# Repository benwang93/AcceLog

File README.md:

AcceLog - Accelerometer Log for Android
=======================================

Android
-------
This project uses the Adafruit MMA8451 breakout board connected to an Arduino Uno. The sensor and Arduino hardware can be easily modified. Eventually a custom board and enclosure should be built.

Links:
- Adafruit MMA8451 webpage:    adafru.it/2019
- Adafruit Arduino libraries:  https://learn.adafruit.com/adafruit-mma8451-accelerometer-breakout/wiring-and-test

The Arduino code and libraries are included in the Arduino folder in this repository.

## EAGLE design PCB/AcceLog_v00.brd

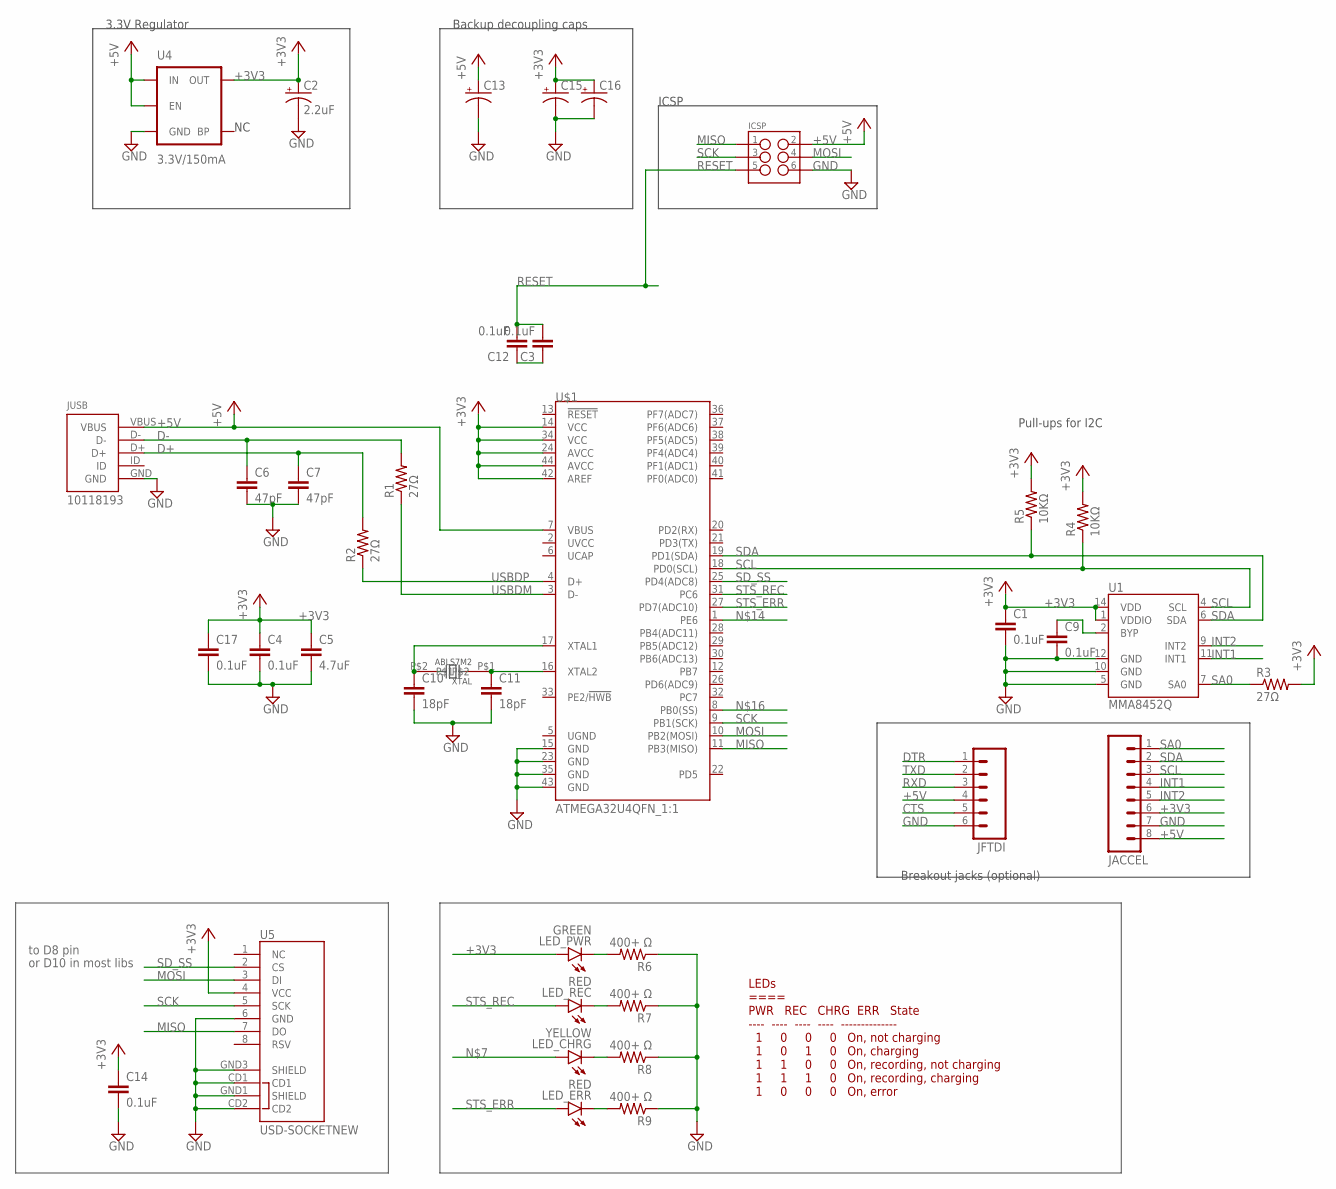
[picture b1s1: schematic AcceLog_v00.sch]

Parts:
C1, C3, C4, C9, C12, C14, C17: 0.1uF; 0603-CAP
C2: 2.2uF; EIA3216
C5: 4.7uF; 0603-CAP
C6, C7: 47pF; 0603-CAP
C10, C11: 18pF; 0603-CAP
C13, C15, C16: CPOL-USE2-5; E2-5
ICSP: M03X22X3_SILK_MALE_PTH; 2X3
JACCEL: M08LOCK; 1X08_LOCK
JFTDI: M06LOCK; 1X06_LOCK
JUSB: 10118193
LED_CHRG: YELLOW; LED-0603
LED_ERR: RED; LED-0603
LED_PWR: GREEN; LED-0603
LED_REC: RED; LED-0603
R1, R2, R3: 27Ω; 0603-RES
R4, R5: 10KΩ; 0603-RES
R6, R7, R8, R9: 400+ Ω; 0603-RES
U1: MMA8452Q; QFN-16_0.5MM
U4: 3.3V/150mA; SOT23-5
U5: USD-SOCKETNEW; MICRO-SD-SOCKET-PP
U$1: ATMEGA32U4QFN_1:1; QFN-44-NOPAD_1:1
XTAL: ABLS7M2

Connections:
+3V3: C1.1, C2.A (+), C4.1, C5.1, C14.1, C15.+, C16.+, C17.1, JACCEL.6, LED_PWR.A, R3.2, R4.2, R5.2, U1.1 (VDDIO), U1.14 (VDD), U4.5 (OUT), U5.4 (VCC), U$1.14 (VCC), U$1.24 (AVCC), U$1.34 (VCC), U$1.42 (AREF), U$1.44 (AVCC)
+5V: C13.+, ICSP.2, JACCEL.8, JFTDI.4, JUSB.VBUS, U4.1 (IN), U4.3 (EN), U$1.7 (VBUS)
CTS: JFTDI.5
D+: C7.1, JUSB.D+, R2.2
D-: C6.1, JUSB.D-, R1.2
DTR: C3.1, C12.1, JFTDI.1
GND: C1.2, C2.C (-), C4.2, C5.2, C6.2, C7.2, C9.2, C10.2, C11.2, C13.-, C14.2, C15.-, C16.-, C17.2, ICSP.6, JACCEL.7, JFTDI.6, JUSB.GND, R6.1, R7.1, R8.1, R9.1, U1.5 (GND), U1.10 (GND), U1.12 (GND), U4.2 (GND), U5.6 (GND), U5.CD1, U5.CD2, U5.GND1 (SHIELD), U5.GND3 (SHIELD), U$1.15 (GND), U$1.23 (GND), U$1.35 (GND), U$1.43 (GND)
INT1: JACCEL.4, U1.11 (INT1)
INT2: JACCEL.5, U1.9 (INT2)
MISO: ICSP.1, U5.7 (DO), U$1.11 (PB3(MISO))
MOSI: ICSP.4, U5.3 (DI), U$1.10 (PB2(MOSI))
unnamed: LED_PWR.C, R6.2
unnamed: LED_REC.C, R7.2
unnamed: LED_CHRG.C, R8.2
unnamed: LED_ERR.C, R9.2
unnamed: C10.1, U$1.17 (XTAL1), XTAL.P$2
unnamed: C9.1, U1.2 (BYP)
unnamed: C11.1, U$1.16 (XTAL2), XTAL.P$1
RESET: C3.2, C12.2, ICSP.5
RXD: JFTDI.3
SA0: JACCEL.1, R3.1, U1.7 (SA0)
SCK: ICSP.3, U5.5 (SCK), U$1.9 (PB1(SCK))
SCL: JACCEL.3, R4.1, U1.4 (SCL), U$1.18 (PD0(SCL))
SDA: JACCEL.2, R5.1, U1.6 (SDA), U$1.19 (PD1(SDA))
SD_SS: U5.2 (CS), U$1.25 (PD4(ADC8))
STS_ERR: LED_ERR.A, U$1.27 (PD7(ADC10))
STS_REC: LED_REC.A, U$1.31 (PC6)
TXD: JFTDI.2
USBDM: R1.1, U$1.3 (D-)
USBDP: R2.1, U$1.4 (D+)

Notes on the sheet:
3.3V Regulator
Pull-ups for I2C
ICSP
Backup decoupling caps
Breakout jacks (optional)
LEDs ==== PWR REC CHRG ERR State ---- ---- ---- ---- -------------- 1 0 0 0 On, not charging 1 0 1 0 On, charging 1 1 0 0 On, recording, not charging 1 1 1 0 On, recording, charging 1 0 0 0 On, error
to D8 pin
or D10 in most libs

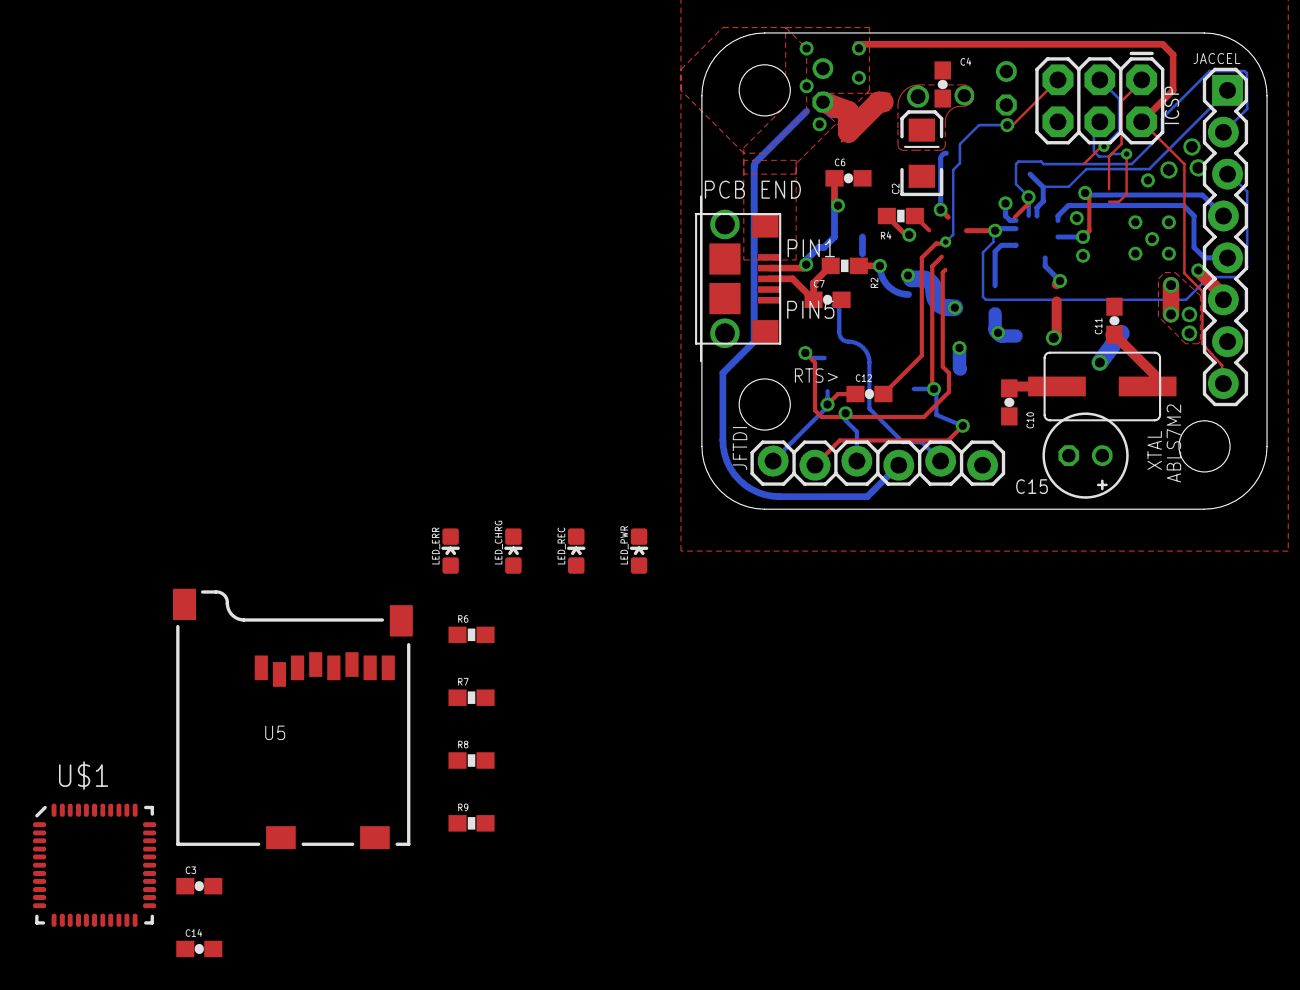
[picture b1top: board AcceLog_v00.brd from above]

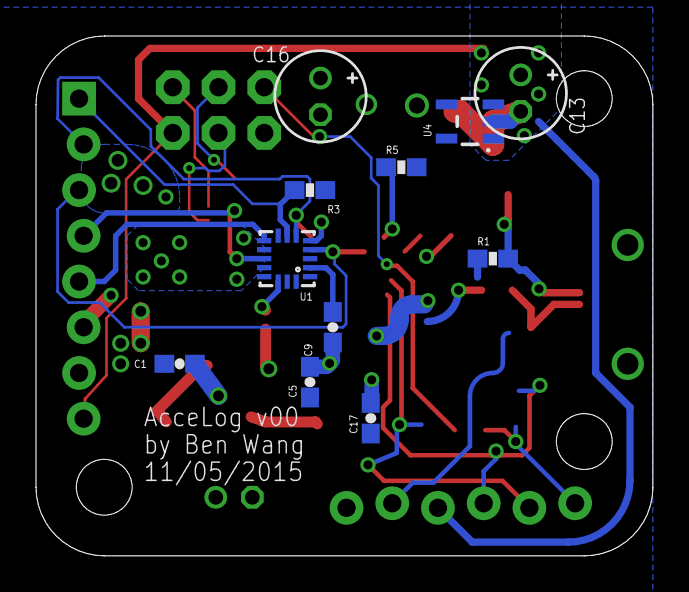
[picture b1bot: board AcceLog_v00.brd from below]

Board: 2 copper layers, 34.3 x 28.9 mm, 38 parts (11 on the bottom side), 27 nets.

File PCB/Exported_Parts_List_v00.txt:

Partlist

Exported from AcceLog_v01.sch at 11/5/2015 2:57 PM

EAGLE Version 7.3.0 Copyright (c) 1988-2015 CadSoft

Assembly variant: 

Part     Value           Device                 Package      Library             Sheet

C1       0.1uF           CAP0603-CAP            0603-CAP     SparkFun-Passives   1
C2       2.2uF           CAP_POL1206            EIA3216      SparkFun-Capacitors 1
C3       0.1uF           CAP0603-CAP            0603-CAP     SparkFun-Passives   1
C4       0.1uF           CAP0603-CAP            0603-CAP     SparkFun-Passives   1
C5       4.7uF           CAP0603-CAP            0603-CAP     SparkFun-Passives   1
C6       47pF            CAP0603-CAP            0603-CAP     SparkFun-Passives   1
C7       47pF            CAP0603-CAP            0603-CAP     SparkFun-Passives   1
C8       100nF           CAP0603-CAP            0603-CAP     SparkFun-Passives   1
C9       0.1uF           CAP0603-CAP            0603-CAP     SparkFun-Passives   1
C10      18pF            CAP0603-CAP            0603-CAP     SparkFun-Passives   1
C11      18pF            CAP0603-CAP            0603-CAP     SparkFun-Passives   1
C12      0.1uF           CAP0603-CAP            0603-CAP     SparkFun-Passives   1
C13                      CPOL-USE2-5            E2-5         rcl                 1
C15                      CPOL-USE2-5            E2-5         rcl                 1
C16                      CPOL-USE2-5            E2-5         rcl                 1
C17      0.1uF           CAP0603-CAP            0603-CAP     SparkFun-Passives   1
ICSP                     M03X22X3_SILK_MALE_PTH 2X3          SparkFun-Connectors 1
JACCEL                   M08LOCK                1X08_LOCK    SparkFun-Connectors 1
JFTDI                    M06LOCK                1X06_LOCK    SparkFun-Connectors 1
JUSB     10118193        10118193               10118193     MicroUSB            1
R1       27?             RESISTOR0603-RES       0603-RES     SparkFun-Passives   1
R2       27?             RESISTOR0603-RES       0603-RES     SparkFun-Passives   1
R3       27?             RESISTOR0603-RES       0603-RES     SparkFun-Passives   1
R4       10K?            RESISTOR0603-RES       0603-RES     SparkFun-Passives   1
R5       10K?            RESISTOR0603-RES       0603-RES     SparkFun-Passives   1
U1       MMA8452Q        MMA8452Q               QFN-16_0.5MM SparkFun-Sensors    1
U2       FTS31XS-U       FT231XS                SSOP20_L     SparkFun-DigitalIC  1
U3       ATMEGA328P_TQFP ATMEGA328P_TQFP        TQFP32-08    SparkFun-DigitalIC  1
U4       3.3V/150mA      V_REG_MIC52053.3V      SOT23-5      SparkFun-PowerIC    1
XTAL     ABLS7M2         ABLS7M2                ABLS7M2      AcceLogLib          1

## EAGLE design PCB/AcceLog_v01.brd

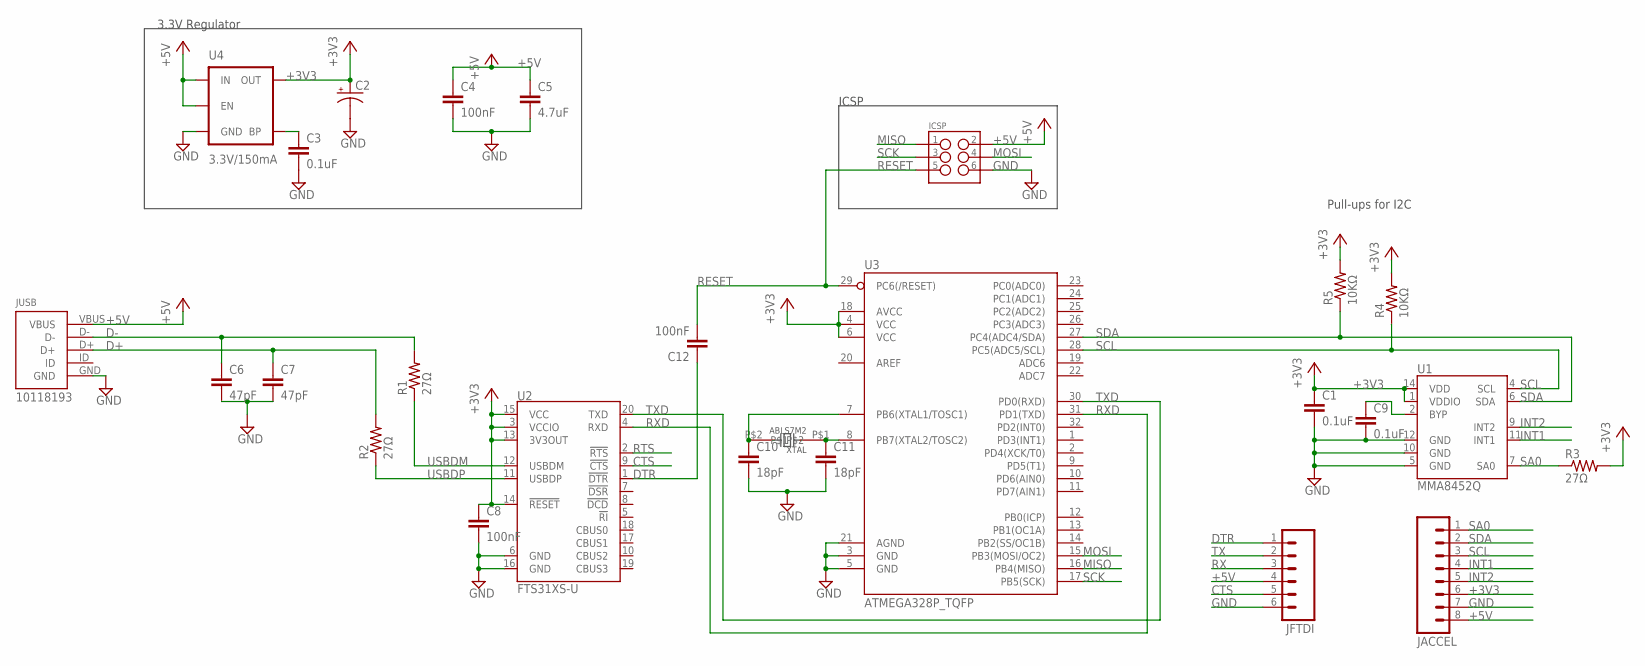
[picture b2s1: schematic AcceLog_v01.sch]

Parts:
C1, C3, C9: 0.1uF; 0603-CAP
C2: CAP_POL1206; EIA3216
C4, C8, C12: 100nF; 0603-CAP
C5: 4.7uF; 0603-CAP
C6, C7: 47pF; 0603-CAP
C10, C11: 18pF; 0603-CAP
ICSP: M03X22X3_SILK_MALE_PTH; 2X3
JACCEL: M08LOCK; 1X08_LOCK
JFTDI: M06LOCK; 1X06_LOCK
JUSB: 10118193
R1, R2, R3: 27Ω; 0603-RES
R4, R5: 10KΩ; 0603-RES
U1: MMA8452Q; QFN-16_0.5MM
U2: FTS31XS-U; SSOP20_L
U3: ATMEGA328P_TQFP; TQFP32-08
U4: 3.3V/150mA; SOT23-5
XTAL: ABLS7M2

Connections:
+3V3: C1.1, C2.A (+), C8.1, JACCEL.6, R3.2, R4.2, R5.2, U1.1 (VDDIO), U1.14 (VDD), U2.3 (VCCIO), U2.13 (3V3OUT), U2.14 (!RESET), U2.15 (VCC), U3.4 (VCC), U3.6 (VCC), U3.18 (AVCC), U4.5 (OUT)
+5V: C4.1, C5.1, ICSP.2, JACCEL.8, JFTDI.4, JUSB.VBUS, U4.1 (IN), U4.3 (EN)
CTS: JFTDI.5, U2.9 (!CTS)
D+: C7.1, JUSB.D+, R2.2
D-: C6.1, JUSB.D-, R1.2
DTR: C12.1, JFTDI.1, U2.1 (!DTR)
GND: C1.2, C2.C (-), C3.2, C4.2, C5.2, C6.2, C7.2, C8.2, C9.2, C10.2, C11.2, ICSP.6, JACCEL.7, JFTDI.6, JUSB.GND, U1.5 (GND), U1.10 (GND), U1.12 (GND), U2.6 (GND), U2.16 (GND), U3.3 (GND), U3.5 (GND), U3.21 (AGND), U4.2 (GND)
INT1: JACCEL.4, U1.11 (INT1)
INT2: JACCEL.5, U1.9 (INT2)
MISO: ICSP.1, U3.16 (PB4(MISO))
MOSI: ICSP.4, U3.15 (PB3(MOSI/OC2))
unnamed: C3.1, U4.4 (BP)
unnamed: C10.1, U3.7 (PB6(XTAL1/TOSC1)), XTAL.P$2
unnamed: C9.1, U1.2 (BYP)
unnamed: C11.1, U3.8 (PB7(XTAL2/TOSC2)), XTAL.P$1
RESET: C12.2, ICSP.5, U3.29 (PC6(/RESET))
RTS: U2.2 (!RTS)
RX: JFTDI.3
RXD: U2.4 (RXD), U3.31 (PD1(TXD))
SA0: JACCEL.1, R3.1, U1.7 (SA0)
SCK: ICSP.3, U3.17 (PB5(SCK))
SCL: JACCEL.3, R4.1, U1.4 (SCL), U3.28 (PC5(ADC5/SCL))
SDA: JACCEL.2, R5.1, U1.6 (SDA), U3.27 (PC4(ADC4/SDA))
TX: JFTDI.2
TXD: U2.20 (TXD), U3.30 (PD0(RXD))
USBDM: R1.1, U2.12 (USBDM)
USBDP: R2.1, U2.11 (USBDP)

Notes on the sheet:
3.3V Regulator
Pull-ups for I2C
ICSP

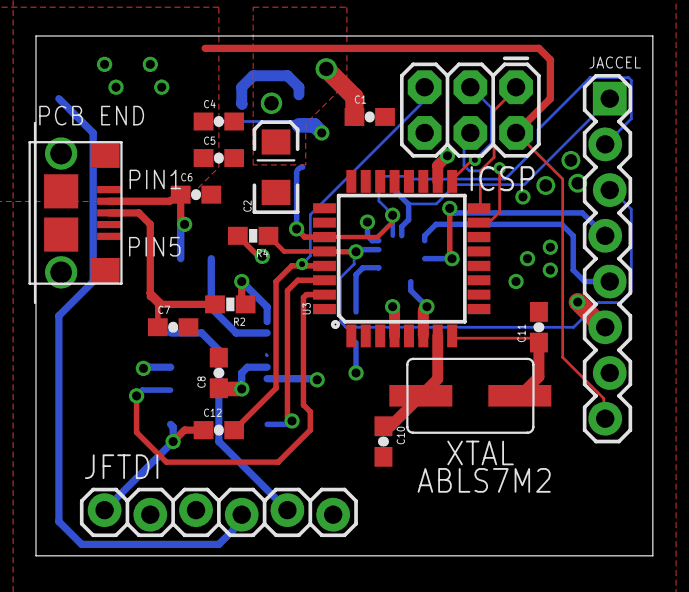
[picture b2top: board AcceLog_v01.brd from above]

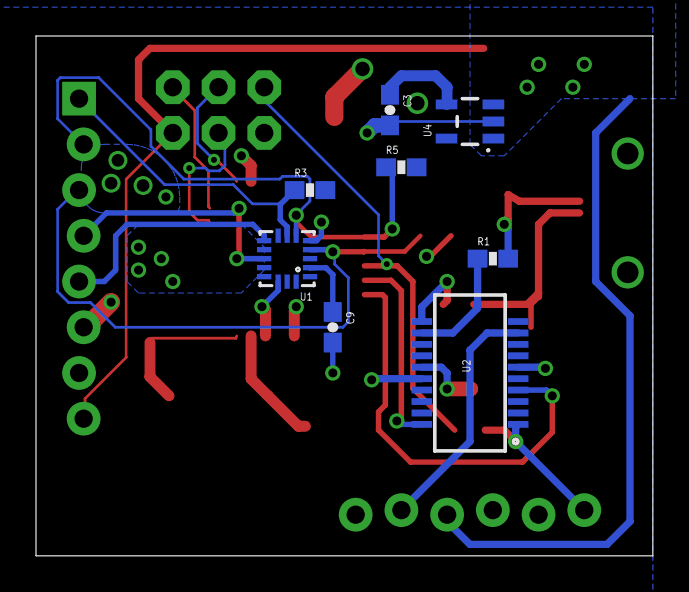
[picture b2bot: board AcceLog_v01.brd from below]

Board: 2 copper layers, 34.3 x 28.9 mm, 26 parts (8 on the bottom side), 24 nets.

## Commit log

2015-09-07 Initial commit: Working serial monitor
2015-09-08 included Arduino code
2015-09-08 basic file save complete
2015-09-10 working on implementing packets
2015-09-10 Untested: initial implementation of packet parsing
2015-09-11 Working CSV save feature. disabled some debug print in console
2015-09-11 set up chart library
2015-09-11 working on graphics. doesn't crash, but chart disappears...
2015-09-11 working graphical log, but app crashes seconds in...
2015-09-11 updated filename to save with start time of activity
2015-09-13 chart plots negative now, disabled start at 0
2015-09-13 working line colors and dataset names
2015-09-13 working chart, with clean lines
2015-09-14 Start/Stop button functional, surpresses keyboard on start
2015-09-15 added Save option to context menu
2015-09-15 added debug view toggle button
2015-09-15 changed baud rate 9600 to 115200. app crashes now from too much data... in graph maybe
2015-09-18 started PCB design
2015-09-19 worked on board more
2015-09-21 initial oscope. works, but crashes
2015-09-23 ability to keep N most recent points. doesn't crash after over 10 min now with higher baud rate
2015-09-23 milliseconds shown in graph, frame skip, 19200 baud
2015-09-24 Implemented async save and progress bar, bug fix for malformed packet
2015-09-24 made constants for defining baud rate
2015-10-02 updated backend for binary data transfer, 19200 baud, eliminate packet type, add sample period TODO: add timestamp/deltaT to packet
2015-10-02 timestamp from Arduino now, will work up to 25 days of recording. Millis save in .csv too
2015-10-03 upped baud rate to 57600, bc 115200 crashes phone. added data analysis
2015-10-03 updated analysis with frequency and file size analysis
2015-10-13 moved packet parsing into service
2015-10-28 fixed right axis of graph
2015-10-28 Added ability to set frameskip at runtime
2015-10-28 updated frameskip dev UI
2015-10-29 added basic icon
2015-11-04 initial schematic, working on initial board
2015-11-04 initial board routed
2015-11-05 AcceLog_v00 Order Placed
2015-11-05 Renamed README to Markdown
2015-12-15 added some LEDs and parts
2015-12-15 worked on documentation/brainstorm for v01
2015-12-16 updated design with MicroSD connections (still have to check footprint)
2015-12-24 added Atmega32u4 to schematic, not done

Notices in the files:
parts and their libraries:
SparkFun-Sensors: Licensing: Creative Commons ShareAlike 4.0 International - https://creativecommons.org/licenses/by-sa/4.0
